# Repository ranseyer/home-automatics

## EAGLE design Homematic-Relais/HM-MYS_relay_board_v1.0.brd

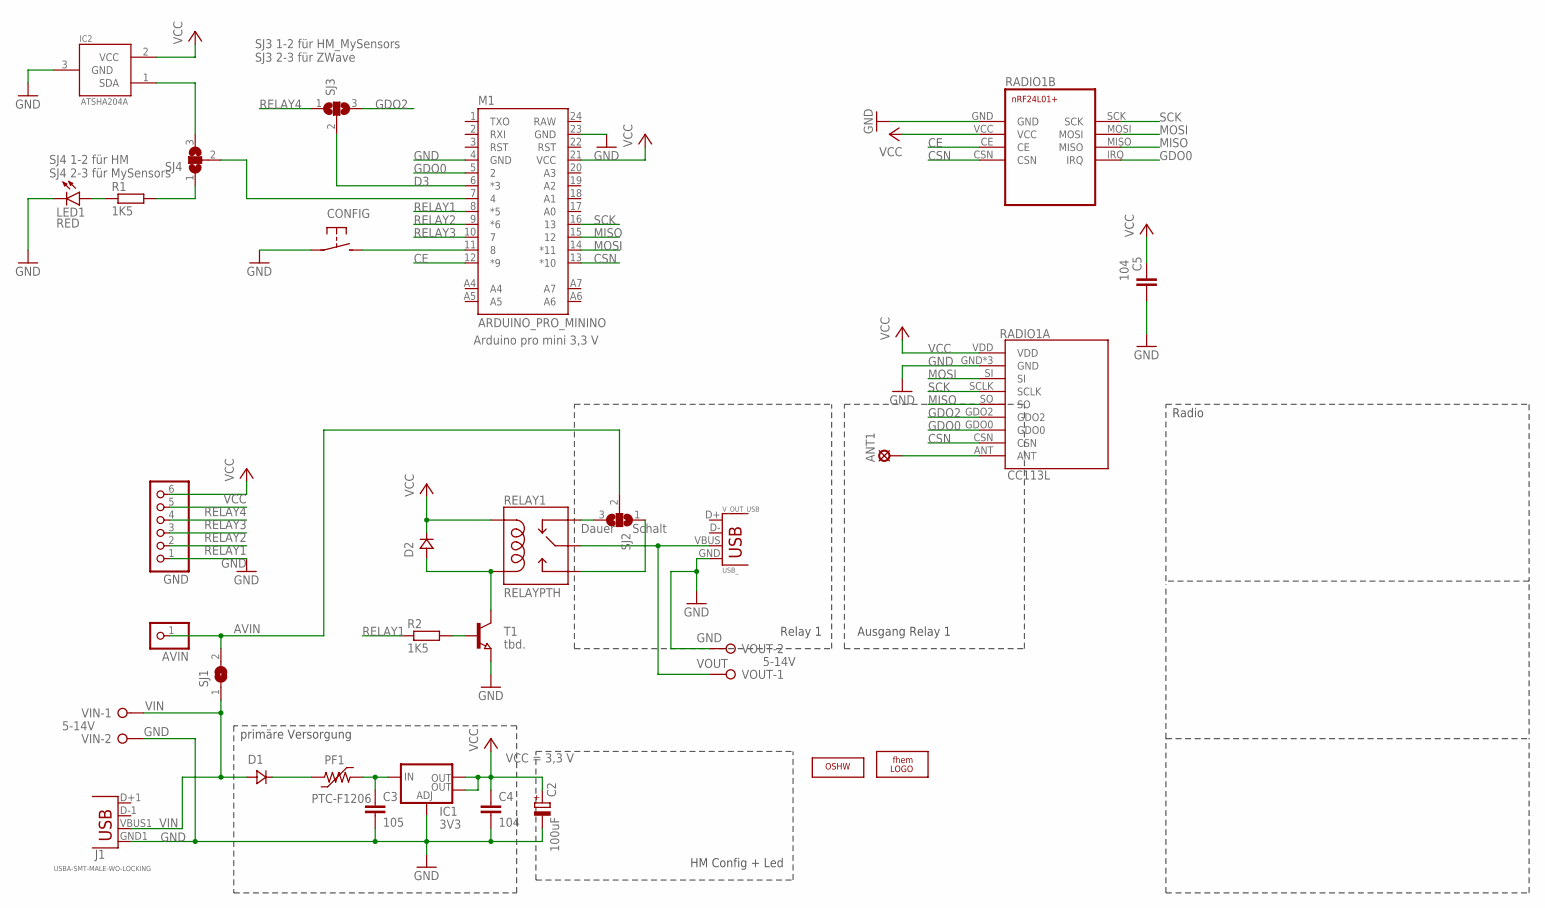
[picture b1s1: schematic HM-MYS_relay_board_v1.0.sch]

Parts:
ANT1: LSP10
AVIN: PINHD-1X1; 1X01
C2: 100uF; E2,5-6E
C3: 105; C0805
C4, C5: 104; C0805
CONFIG: TASTER-SMD
D1, D2: SS14; DO214
GND: PINHD-1X6_S; 1X06
IC1: 3V3; SOT223
IC2: ATSHA204A; SOT23-3
J1: USBA-SMT-MALE-WO-LOCKING; USB-A-SMT-MALE-NO_LOCKING
LED1: RED; LED-1206
LOGO2: LOGO_OSHWX0070; OSHW_6X70
M1: ARDUINO_PRO_MININO; ARDUINO_PRO_MINI_O
PF1: PTC-F1206; F1206
R1, R2: 1K5; R0805_SMALL_GAP
RADIO1A: CC113L
RADIO1B: NRF24L01+NRF24L01+MINI; NRF24L01+MINI
RELAY1: RELAYPTH; SRD-05VDC-SL-C
SJ1: SJ
SJ2, SJ3, SJ4: SJ2W; SJ_2
T1: tbd.; SOT89
U$2: LOGO_FHEMSTOP; LOGO_FHEM_3X3_STOP
VIN: W237-132
VOUT: W237-132
V_OUT_USB: USB_; USB-A-S-SILK-FEMALE

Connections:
ATSHA: IC2.1 (SDA), SJ4.3
AVIN: AVIN.1, SJ1.2, SJ2.2
CE: M1.12 (*9), RADIO1B.CE
CSN: M1.13 (*10), RADIO1A.CSN, RADIO1B.CSN
D3: M1.6 (*3), SJ3.2
D4: M1.7 (4), SJ4.2
DAUER: RELAY1.SWCLOSED (SWCLOSE), SJ2.3
GDO0: M1.5 (2), RADIO1A.GDO0, RADIO1B.IRQ
GDO2: RADIO1A.GDO2, SJ3.3
GND: C2.-, C3.2, C4.2, C5.2, CONFIG.1, GND.1, IC1.1 (ADJ), IC2.3 (GND), J1.GND1 (GND), LED1.C, M1.4 (GND), M1.23 (GND), RADIO1A.GND, RADIO1A.GND1 (GND), RADIO1A.GND2 (GND), RADIO1B.GND, T1.3 (E), VIN.2, VOUT.2, V_OUT_USB.GND
LED: R1.2, SJ4.1
MISO: M1.15 (12), RADIO1A.SO, RADIO1B.MISO
MOSI: M1.14 (*11), RADIO1A.SI, RADIO1B.MOSI
unnamed: CONFIG.2 (S), M1.11 (8)
unnamed: LED1.A, R1.1
unnamed: ANT1.1, RADIO1A.ANT
unnamed: D2.ANODE, RELAY1.COIL0, T1.2 (C)
unnamed: R2.2, T1.1 (B)
RELAY1: GND.2, M1.8 (*5), R2.1
RELAY2: GND.3, M1.9 (*6)
RELAY3: GND.4, M1.10 (7)
RELAY4: GND.5, SJ3.1
SCHALT: RELAY1.SWOPEN, SJ2.1
SCK: M1.16 (13), RADIO1A.SCLK, RADIO1B.SCK
VCC: C2.+, C4.1, C5.1, D2.CATHODE, GND.6, IC1.2 (OUT), IC1.4 (OUT), IC2.2 (VCC), M1.21 (VCC), RADIO1A.VDD, RADIO1B.VCC, RELAY1.COIL1
VIN: D1.ANODE, J1.VBUS1 (VBUS), SJ1.1, VIN.1
VOUT: RELAY1.SWCOMMON, VOUT.1, V_OUT_USB.VBUS
VREG_IN: C3.1, IC1.3 (IN), PF1.2
VUSB: D1.CATHODE, PF1.1

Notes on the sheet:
primäre Versorgung
5-14V
Radio
HM Config + Led
Relay 1
Ausgang Relay 1
Dauer
Schalt
SJ3 1-2 für HM_MySensors SJ3 2-3 für ZWave
Arduino pro mini 3,3 V
VCC = 3,3 V
SJ4 1-2 für HM SJ4 2-3 für MySensors

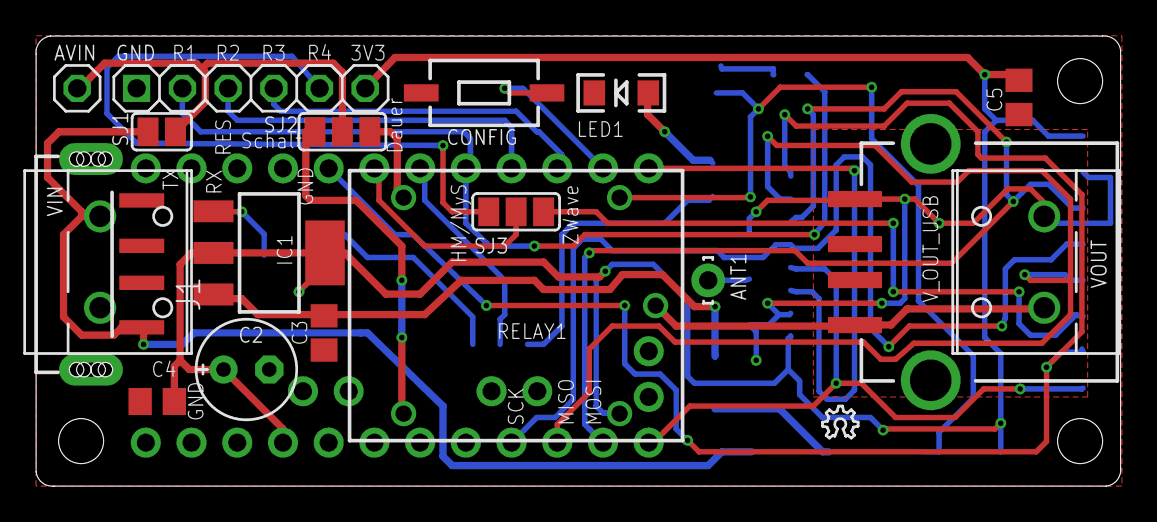
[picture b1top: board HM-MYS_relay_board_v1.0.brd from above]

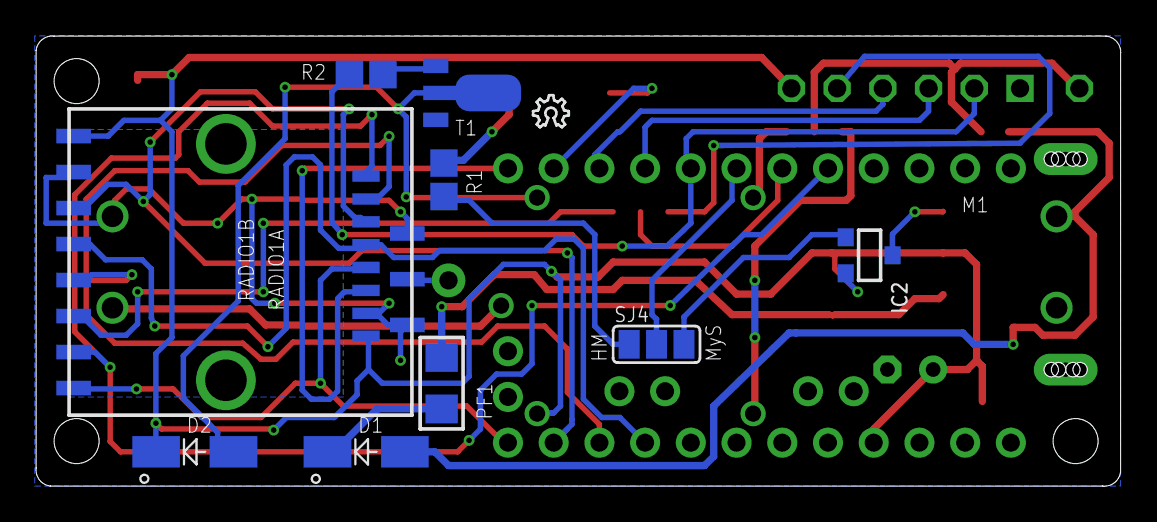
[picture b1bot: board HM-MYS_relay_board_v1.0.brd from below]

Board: 2 copper layers, 60.3 x 25.0 mm, 32 parts (12 on the bottom side), 29 nets.

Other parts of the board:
LOGO1: LOGO_OSHWX0070; OSHW_6X70

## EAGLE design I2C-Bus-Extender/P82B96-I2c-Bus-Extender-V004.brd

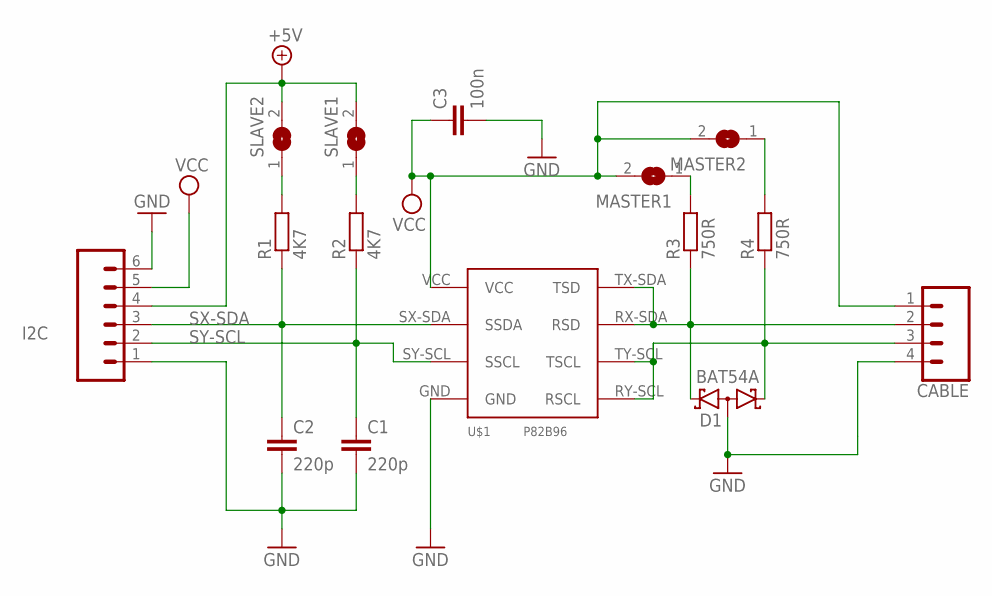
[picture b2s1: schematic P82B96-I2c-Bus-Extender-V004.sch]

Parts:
C1, C2: 220p; C0805K
C3: 100n; C0805K
CABLE: CONN_04LOCK_LONGPADS; 1X04_LOCK_LONGPADS
D1: BAT54A; SOT23
I2C: CONN_06LONGPADS; 1X06_LONGPADS
MASTER1, MASTER2: SJ
R1, R2: 4K7; R0805W
R3, R4: 750R; R0805W
SLAVE1, SLAVE2: SJ
U$1: P82B96-NEW; SOIC8

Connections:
+5V: I2C.4, SLAVE1.2, SLAVE2.2
GND: C1.2, C2.2, C3.2, CABLE.4, D1.3 (AA), I2C.1, I2C.6, U$1.GND
unnamed: R2.2, SLAVE1.1
unnamed: R1.2, SLAVE2.1
unnamed: MASTER2.1, R4.2
unnamed: MASTER1.1, R3.2
unnamed: CABLE.2, D1.2 (K2), R3.1, U$1.RX-SDA (RSD), U$1.TX-SDA (TSD)
unnamed: CABLE.3, D1.1 (K1), R4.1, U$1.RY-SCL (RSCL), U$1.TY-SCL (TSCL)
SX-SDA: C2.1, I2C.3, R1.1, U$1.SX-SDA (SSDA)
SY-SCL: C1.1, I2C.2, R2.1, U$1.SY-SCL (SSCL)
VCC: C3.1, CABLE.1, I2C.5, MASTER1.2, MASTER2.2, U$1.VCC

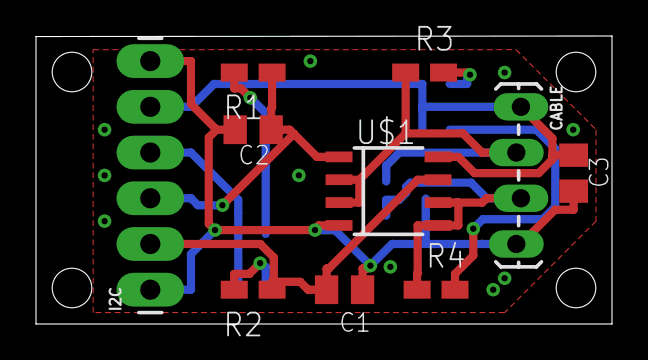
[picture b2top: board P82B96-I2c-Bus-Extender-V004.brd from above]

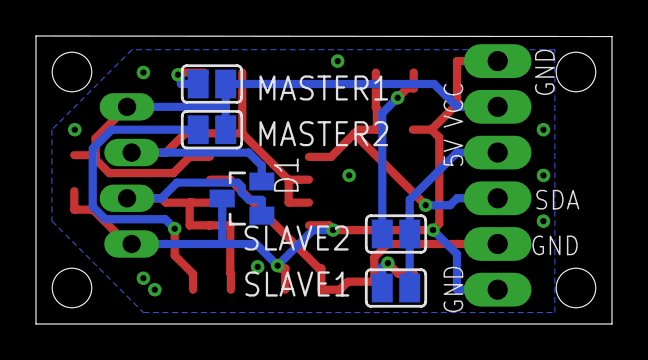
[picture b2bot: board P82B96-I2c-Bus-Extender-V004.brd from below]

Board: 2 copper layers, 32.0 x 16.0 mm, 15 parts (5 on the bottom side), 11 nets.

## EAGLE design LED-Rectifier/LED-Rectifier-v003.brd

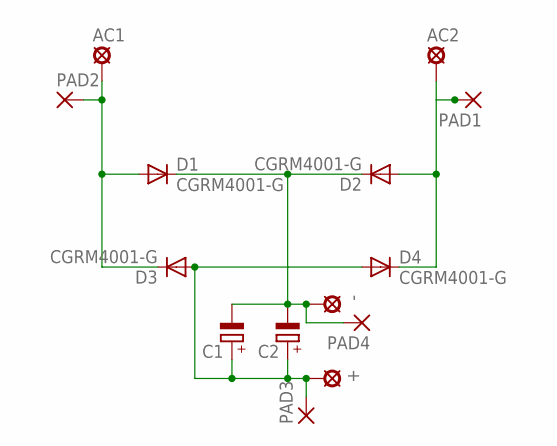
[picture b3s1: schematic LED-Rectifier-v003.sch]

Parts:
+: SE14
-: SE14
AC1, AC2: SE14
C1: CPOL-EU085CS-1AW; 085CS_1AW
C2: CPOL-EUE3.5-10; E3,5-10
D1, D2, D3, D4: CGRM4001-G; SOD-123_MINI-SMA
PAD1, PAD2, PAD3, PAD4: SMD5; SMD2,54-5,08

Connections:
+: +.MP, C1.+, C2.+, D3.A, D4.A, PAD3.1
-: -.MP, C1.-, C2.-, D1.C, D2.C, PAD4.1
AC1: AC1.MP, D1.A, D3.C, PAD2.1
AC2: AC2.MP, D2.A, D4.C, PAD1.1

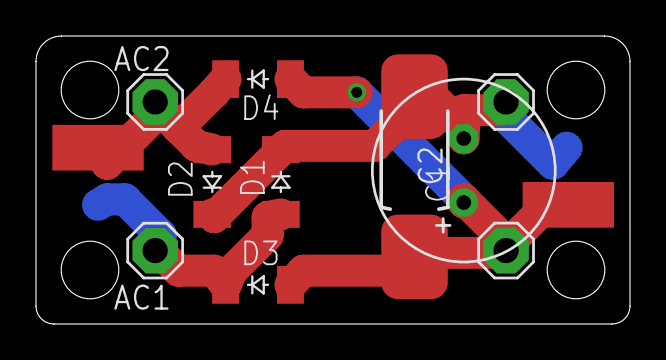
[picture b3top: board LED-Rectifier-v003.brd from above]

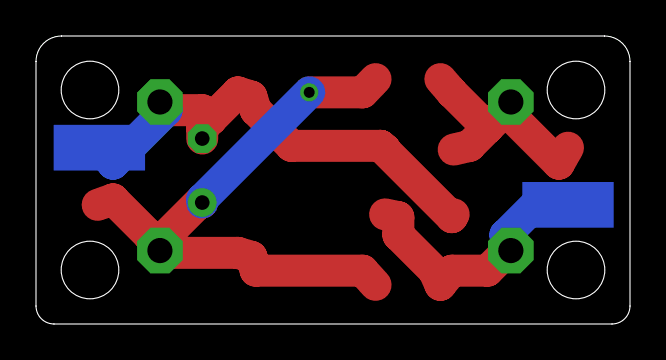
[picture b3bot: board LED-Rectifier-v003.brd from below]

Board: 2 copper layers, 33.0 x 16.0 mm, 14 parts (2 on the bottom side), 4 nets.

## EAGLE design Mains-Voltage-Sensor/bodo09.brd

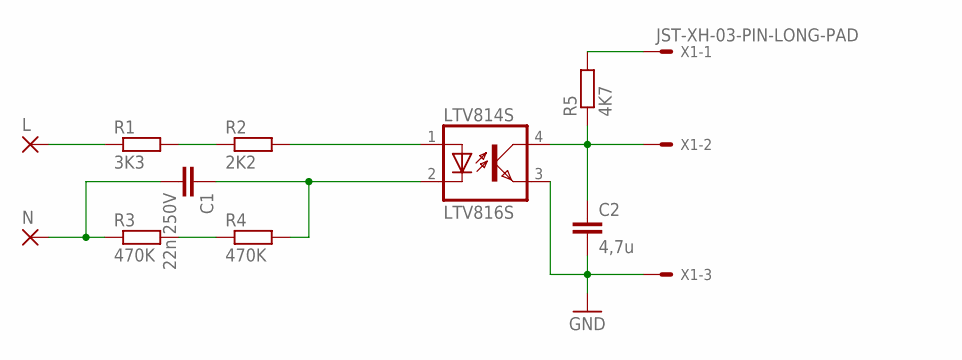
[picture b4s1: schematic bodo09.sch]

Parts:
C1: 22n 250V; C2220K
C2: 4,7u; C1206K
L: 3,81/1,4
LTV814S: LTV816S; SMD4
N: 3,81/1,4
R1: 3K3; R1206
R2: 2K2; R1206
R3, R4: 470K; R1206
R5: 4K7; R0805
X1: JST-XH-03-PIN-LONG-PAD; JST-XH-03-PACKAGE-LONG-PAD

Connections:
GND: C2.2, LTV814S.3 (EMIT), X1.3
unnamed: L.1, R1.1
unnamed: C1.2, N.1, R3.1
unnamed: R3.2, R4.1
unnamed: C1.1, LTV814S.2 (C), R4.2
unnamed: LTV814S.1 (A), R2.2
unnamed: R1.2, R2.1
unnamed: C2.1, LTV814S.4 (COL), R5.1, X1.2
unnamed: R5.2, X1.1

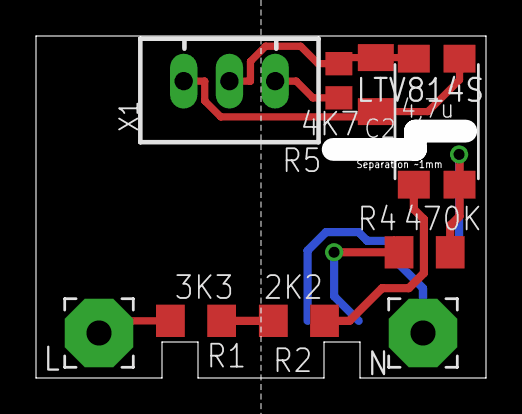
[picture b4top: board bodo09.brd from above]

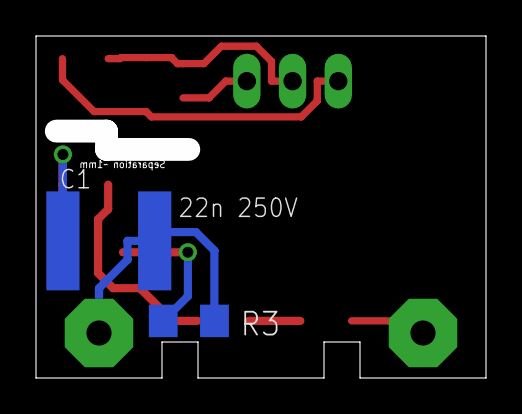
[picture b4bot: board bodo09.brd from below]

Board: 2 copper layers, 25.0 x 19.0 mm, 11 parts (2 on the bottom side), 9 nets.

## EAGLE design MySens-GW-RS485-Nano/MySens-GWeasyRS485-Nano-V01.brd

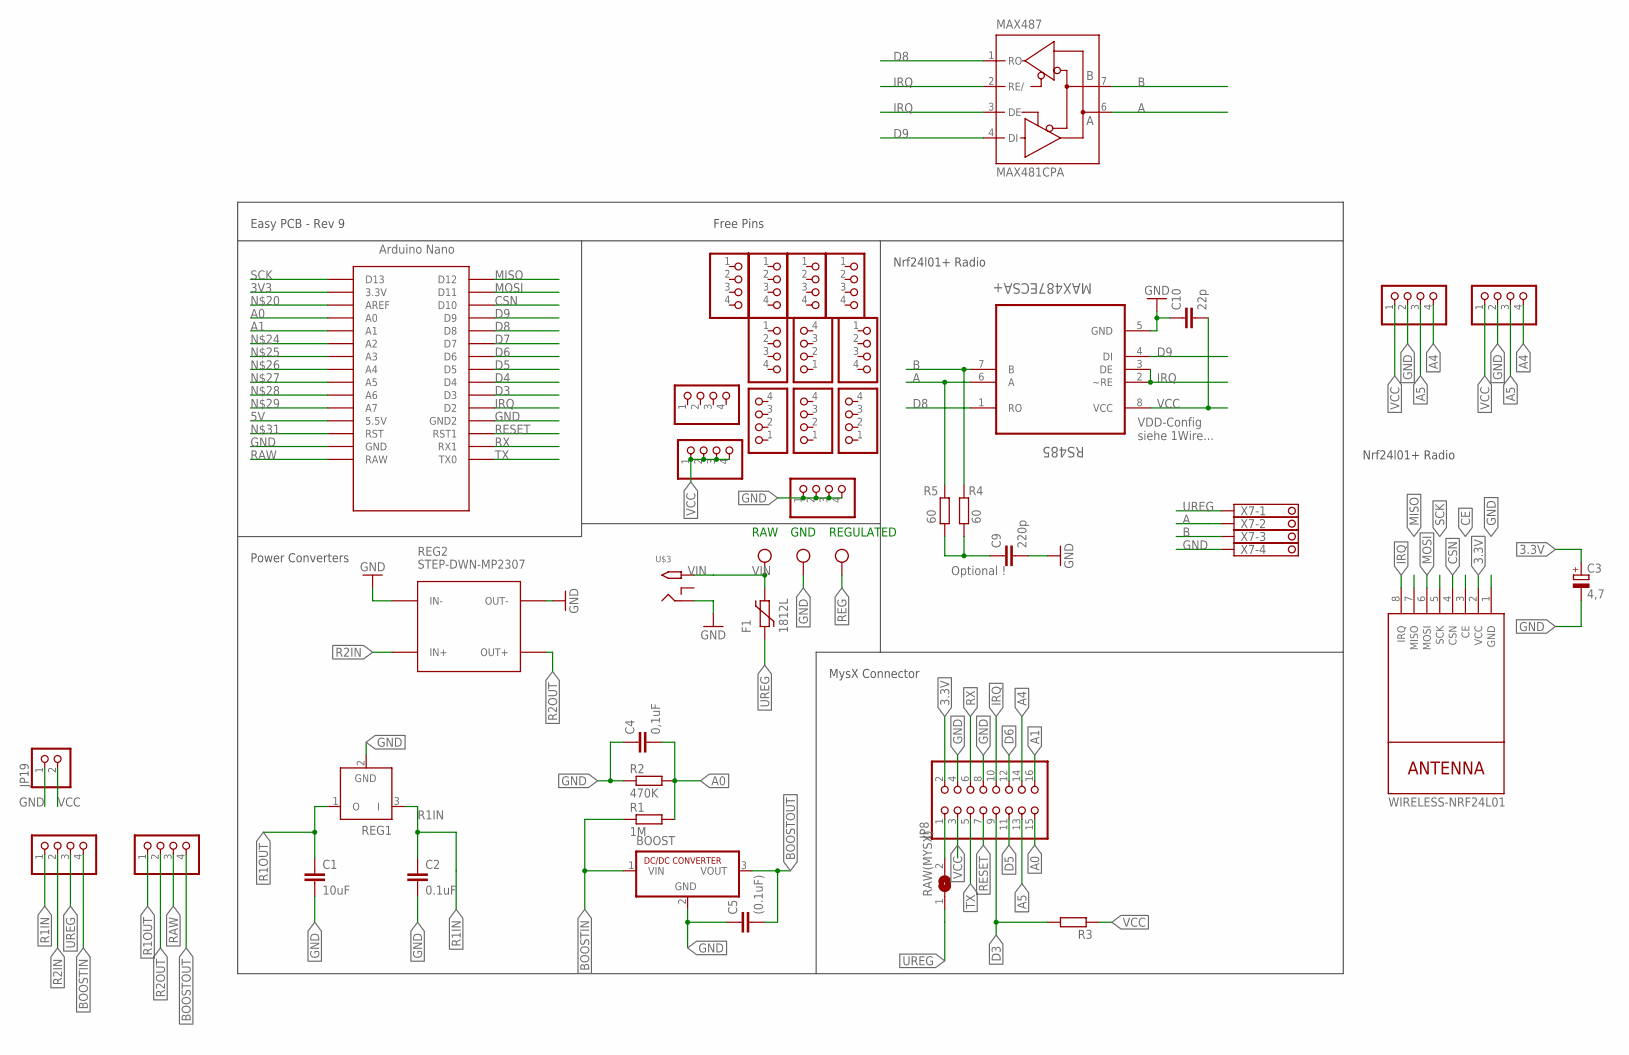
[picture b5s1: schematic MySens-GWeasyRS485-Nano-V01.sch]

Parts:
BOOST: R-78C1.8-1.0; SIP3
C1: 10uF; C1210
C2: 0.1uF; C1206
C3: 4,7; SMC_C
C4: 0,1uF; C1206
C5: (0.1uF); C1206
C9: 220p; C0805
C10: 22p; C0805
F1: 1812L
JP1, JP2, JP3, JP4, JP5, JP6, JP7, JP9, JP10, JP11, JP12, JP13, JP14, JP15, JP16, JP17, JP18: PINHD-1X04_2.54-S; 1X04-S
JP8: PINHD-2X08_2.54; 2X08
JP19: PINHD-1X2; 1X02
MAX487: MAX481CPA; DIL08
NRF24L01+: WIRELESS-NRF24L01
R1: 1M; R0805
R2: 470K; R0805
R3: R-EU_R0805; R0805
R4, R5: 60; R0805
RAW(MYSX): SJ
REG1: LP2950Z; TO92
REG2: STEP-DWN-MP2307; DC-DC-STEP-DOWN-MP2307
REGULATED: W237-103
RS485: MAX487ECSA+; SOIC127P600X175-8N
U$2: NANO
U$3: 2.1MMJACKTHM; PJ-102A
X7: 1751264

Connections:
3.3V: C3.+, JP8.2, NRF24L01+.2 (VCC)
3V3: U$2.3.3V
5V: U$2.5V (5.5V)
A: MAX487.6 (A), R5.2, RS485.6 (A), X7.2
A0: C4.2, JP8.15, R1.2, R2.2, U$2.A0
A1: JP8.16, U$2.A1
A4: JP6.4, JP8.14, JP10.4
A5: JP6.3, JP8.13, JP10.3
B: MAX487.7 (B), R4.2, RS485.7 (B), X7.3
BOOSTIN: BOOST.1 (VIN), JP2.4, R1.1
BOOSTOUT: BOOST.3 (VOUT), C5.2, JP4.4
CE: NRF24L01+.3 (CE)
CSN: NRF24L01+.4 (CSN), U$2.D10
D3: JP8.9, R3.2, U$2.D3
D4: U$2.D4
D5: JP8.11, U$2.D5
D6: JP8.12, U$2.D6
D7: U$2.D7
D8: MAX487.1 (RO), RS485.1 (RO), U$2.D8
D9: MAX487.4 (DI), RS485.4 (DI), U$2.D9
GND: BOOST.2 (GND), C1.2, C2.2, C3.-, C4.1, C5.1, C9.2, C10.1, JP1.1, JP1.2, JP1.3, JP1.4, JP6.2, JP8.4, JP8.8, JP10.2, JP19.1, MAX487.5 (GND), NRF24L01+.1 (GND), R2.1, REG1.2 (GND), REG2.IN-, REG2.OUT-, REGULATED.2, RS485.5 (GND), U$2.GND, U$2.GND1 (GND2), U$3.RING, X7.4
IRQ: JP8.10, MAX487.2 (RE/), MAX487.3 (DE), NRF24L01+.8 (IRQ), RS485.2 (~RE), RS485.3 (DE), U$2.D2
MISO: NRF24L01+.7 (MISO), U$2.D12
MOSI: NRF24L01+.6 (MOSI), U$2.D11
unnamed: JP8.1, RAW(MYSX).2
unnamed: C9.1, R4.1, R5.1
R1IN: C2.1, JP2.1, REG1.3 (I)
R1OUT: C1.1, JP4.1, REG1.1 (O)
R2IN: JP2.2, REG2.IN+
R2OUT: JP4.2, REG2.OUT+
RAW: JP4.3, U$2.RAW
REG: REGULATED.1
RESET: JP8.7, U$2.RST1
RX: JP8.6, U$2.RX1
SCK: NRF24L01+.5 (SCK), U$2.D13
TX: JP8.5, U$2.TX0
UREG: F1.P$1 (1), JP2.3, RAW(MYSX).1, X7.1
VCC: C10.2, JP3.1, JP3.2, JP3.3, JP3.4, JP6.1, JP8.3, JP10.1, JP19.2, MAX487.8 (VCC), R3.1, RS485.8 (VCC)
VIN: F1.P$2 (2), REGULATED.3, U$3.TIP

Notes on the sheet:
GND
RAW
REGULATED
Easy PCB - Rev 9
MysX Connector
Nrf24l01+ Radio
Power Converters
Free Pins
VDD-Config siehe 1Wire...
Optional !

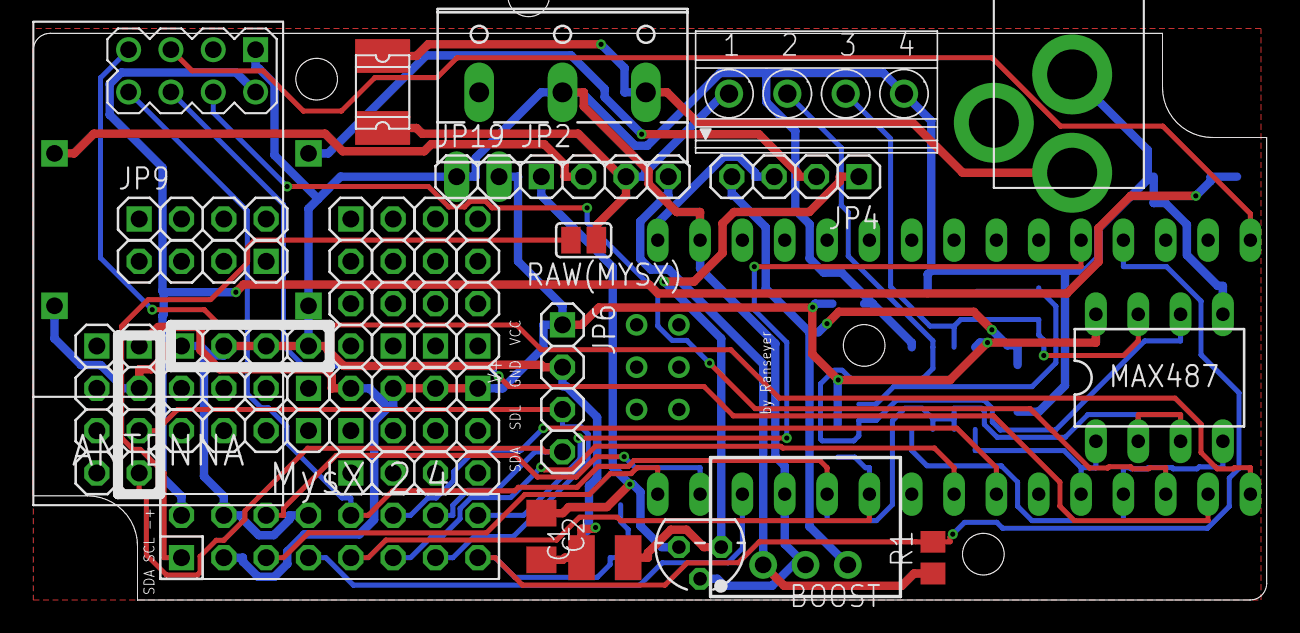
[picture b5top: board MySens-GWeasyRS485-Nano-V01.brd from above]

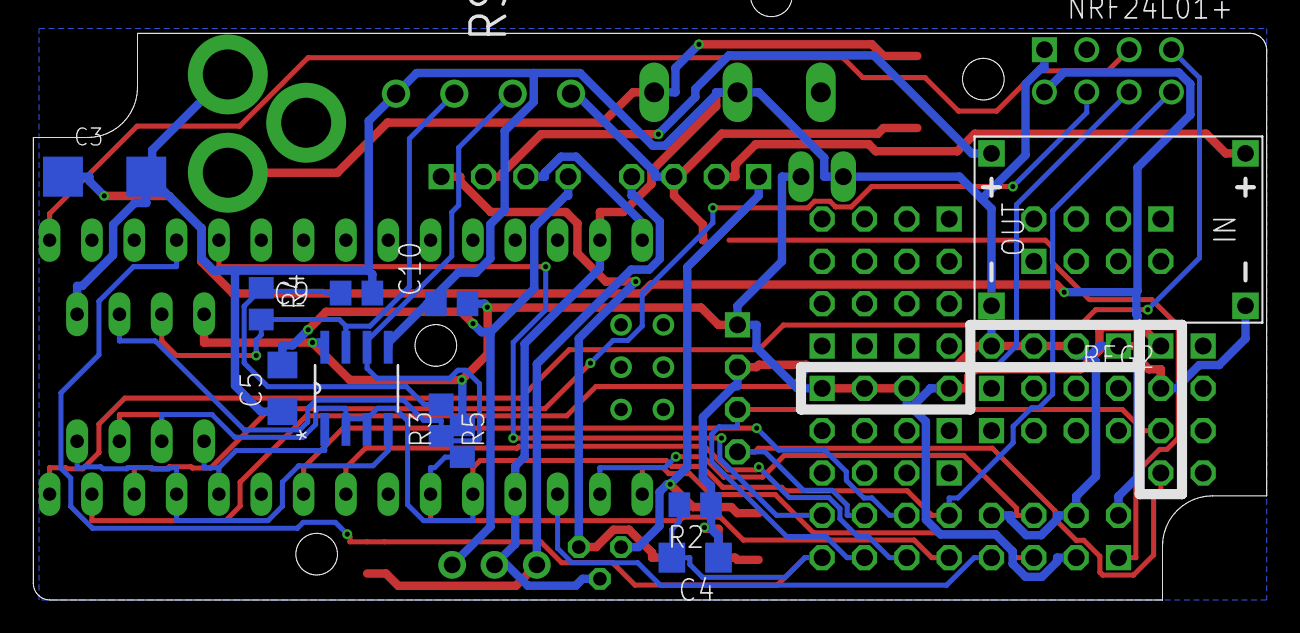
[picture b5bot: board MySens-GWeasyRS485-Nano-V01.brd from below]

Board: 2 copper layers, 74.0 x 34.0 mm, 43 parts (11 on the bottom side), 33 nets.

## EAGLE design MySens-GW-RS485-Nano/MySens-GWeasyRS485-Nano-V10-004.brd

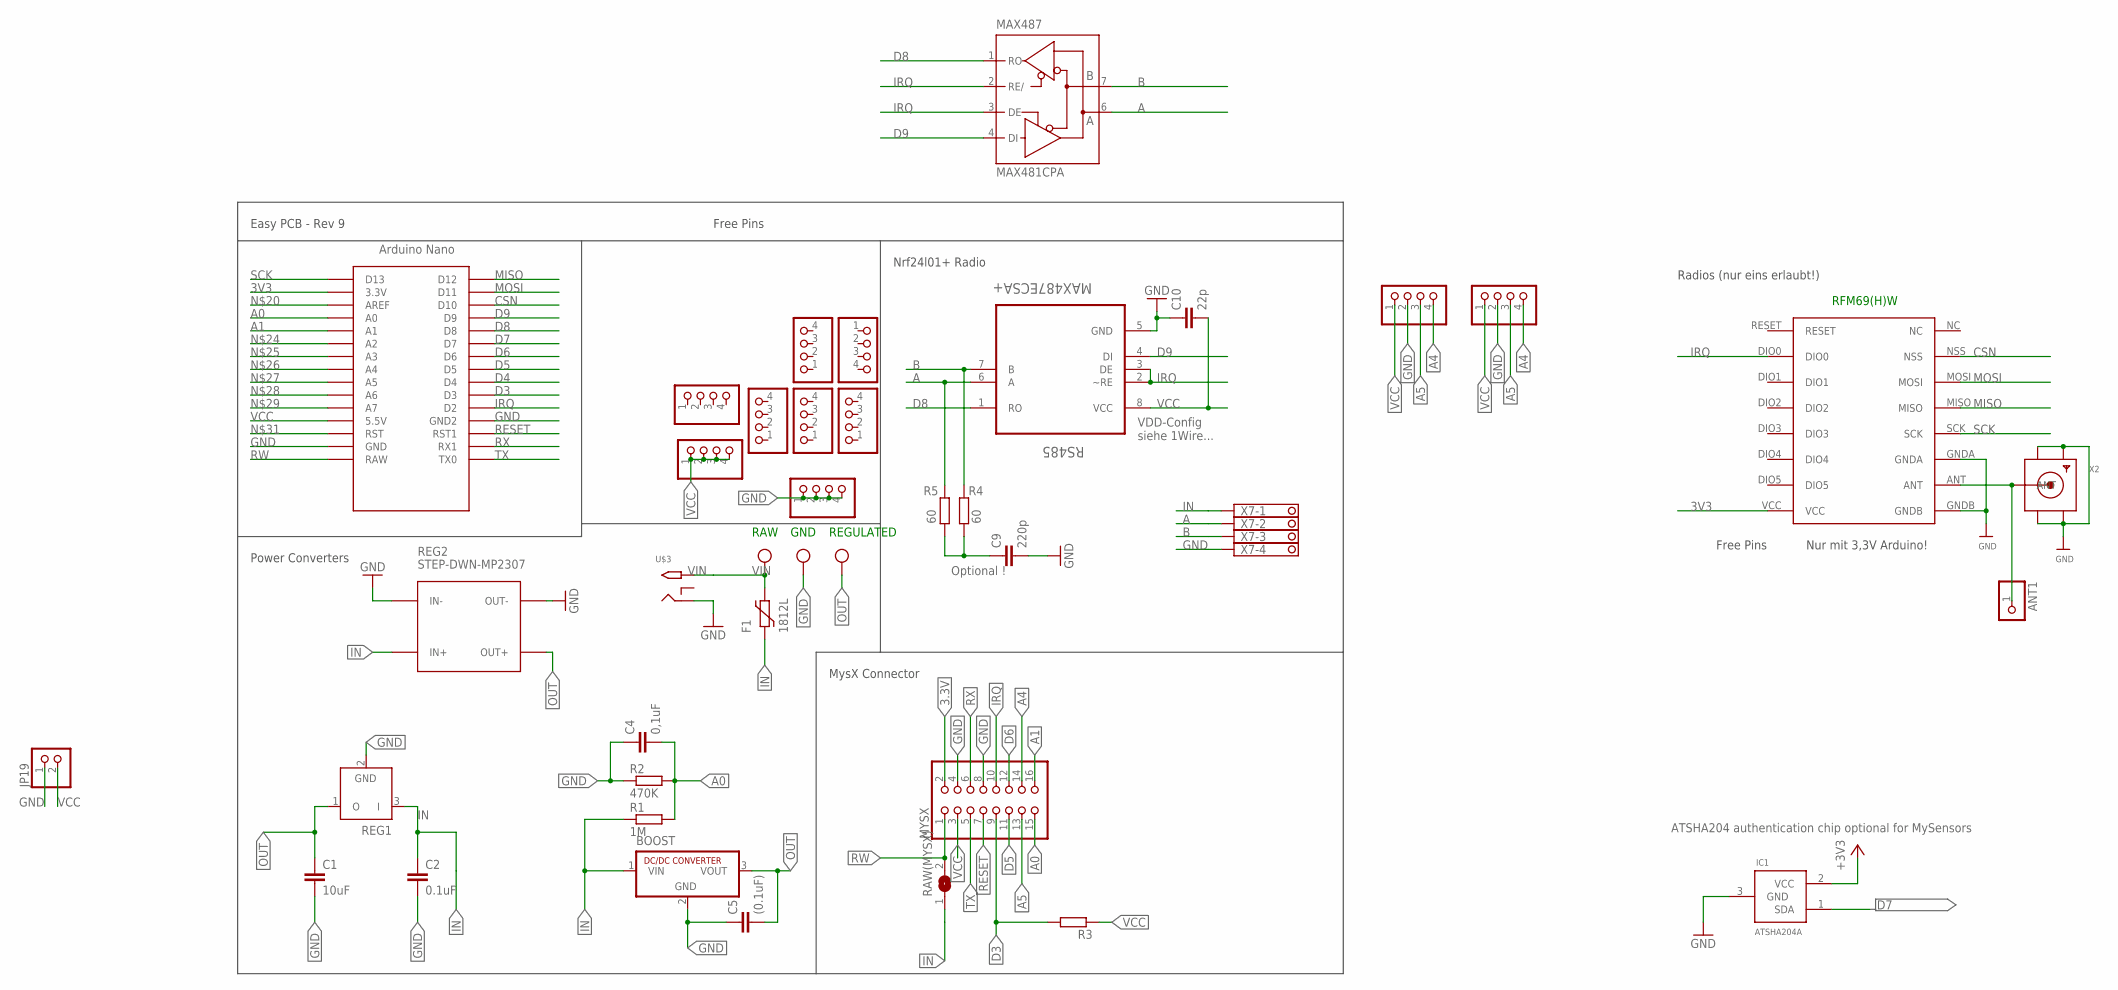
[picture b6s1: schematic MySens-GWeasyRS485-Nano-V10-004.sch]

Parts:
ANT1: PINHD-1X1; 1X01
BOOST: R-78C1.8-1.0; SIP3
C1: 10uF; C1210
C2: 0.1uF; C1206
C4: 0,1uF; C1206
C5: (0.1uF); C1206
C9: 220p; C0805
C10: 22p; C0805
F1: 1812L
IC1: ATSHA204A; SOT23
JP1, JP3, JP6, JP10, JP11, JP12, JP13, JP14, JP15, JP16: PINHD-1X04_2.54-S; 1X04-S
JP19: PINHD-1X2; 1X02
MAX487: MAX481CPA; DIL08
MYSX: PINHD-2X08_2.54; 2X08
R1: 1M; R0805
R2: 470K; R0805
R3: R-EU_R0805; R0805
R4, R5: 60; R0805
RAW(MYSX): SJ
REG1: LP2950Z; TO92
REG2: STEP-DWN-MP2307; DC-DC-STEP-DOWN-MP2307
REGULATED: W237-103
RFM69W: RFM69HW; RFM
RS485: MAX487ECSA+; SOIC127P600X175-8N
U$2: NANO
U$3: 2.1MMJACKTHM; PJ-102A
X2: SMACONNECTOR_EDGE; SMA_EDGELAUNCH
X7: 1751264

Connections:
3.3V: IC1.2 (VCC), MYSX.2
3V3: RFM69W.VCC, U$2.3.3V
A: MAX487.6 (A), R5.2, RS485.6 (A), X7.2
A0: C4.2, MYSX.15, R1.2, R2.2, U$2.A0
A1: MYSX.16, U$2.A1
A4: JP6.4, JP10.4, MYSX.14
A5: JP6.3, JP10.3, MYSX.13
B: MAX487.7 (B), R4.2, RS485.7 (B), X7.3
CSN: RFM69W.NSS, U$2.D10
D3: MYSX.9, R3.2, U$2.D3
D4: U$2.D4
D5: MYSX.11, U$2.D5
D6: MYSX.12, U$2.D6
D7: IC1.1 (SDA), U$2.D7
D8: MAX487.1 (RO), RS485.1 (RO), U$2.D8
D9: MAX487.4 (DI), RS485.4 (DI), U$2.D9
GND: BOOST.2 (GND), C1.2, C2.2, C4.1, C5.1, C9.2, C10.1, IC1.3 (GND), JP1.1, JP1.2, JP1.3, JP1.4, JP6.2, JP10.2, JP19.1, MAX487.5 (GND), MYSX.4, MYSX.8, R2.1, REG1.2 (GND), REG2.IN-, REG2.OUT-, REGULATED.2, RFM69W.GNDA, RFM69W.GNDB, RS485.5 (GND), U$2.GND, U$2.GND1 (GND2), U$3.RING, X2.GND@1 (GND4), X2.GND@2 (GND3), X2.GND@3 (GND2), X2.GND@4 (GND1), X7.4
IN: BOOST.1 (VIN), C2.1, F1.P$1 (1), R1.1, RAW(MYSX).1, REG1.3 (I), REG2.IN+, X7.1
IRQ: MAX487.2 (RE/), MAX487.3 (DE), MYSX.10, RFM69W.DIO0, RS485.2 (~RE), RS485.3 (DE), U$2.D2
MISO: RFM69W.MISO, U$2.D12
MOSI: RFM69W.MOSI, U$2.D11
unnamed: ANT1.1, RFM69W.ANT, X2.P (ANT)
unnamed: C9.1, R4.1, R5.1
OUT: BOOST.3 (VOUT), C1.1, C5.2, REG1.1 (O), REG2.OUT+, REGULATED.1
RESET: MYSX.7, U$2.RST1
RW: MYSX.1, RAW(MYSX).2, U$2.RAW
RX: MYSX.6, U$2.RX1
SCK: RFM69W.SCK, U$2.D13
TX: MYSX.5, U$2.TX0
VCC: C10.2, JP3.1, JP3.2, JP3.3, JP3.4, JP6.1, JP10.1, JP19.2, MAX487.8 (VCC), MYSX.3, R3.1, RS485.8 (VCC), U$2.5V (5.5V)
VIN: F1.P$2 (2), REGULATED.3, U$3.TIP

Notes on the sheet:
GND
RAW
REGULATED
Easy PCB - Rev 9
MysX Connector
Nrf24l01+ Radio
Power Converters
Free Pins
VDD-Config siehe 1Wire...
Optional !
ATSHA204 authentication chip optional for MySensors
RFM69(H)W
Nur mit 3,3V Arduino!
Radios (nur eins erlaubt!)

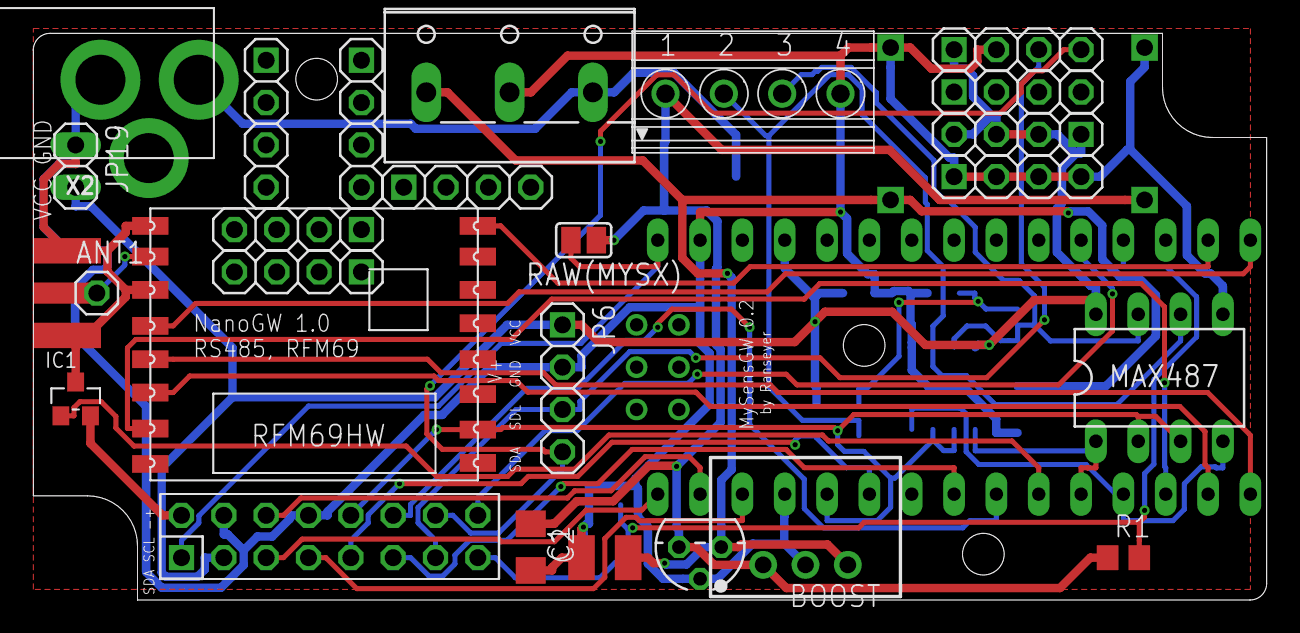
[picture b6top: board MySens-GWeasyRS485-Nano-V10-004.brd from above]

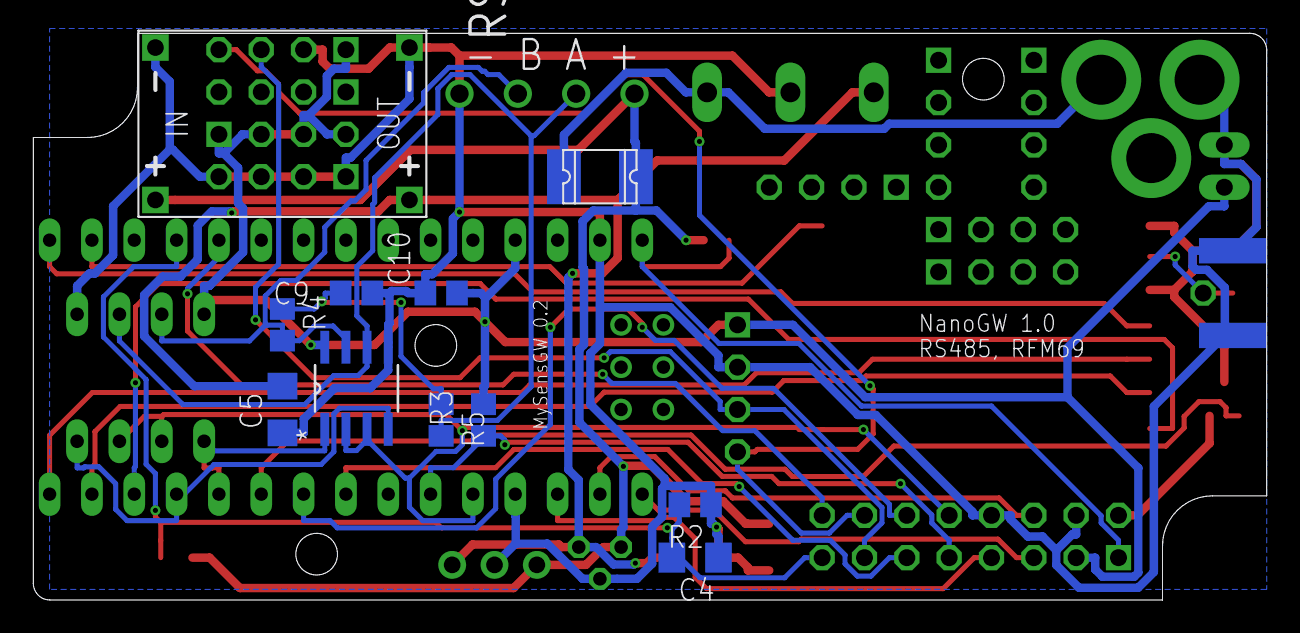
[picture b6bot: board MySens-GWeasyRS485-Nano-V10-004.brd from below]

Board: 2 copper layers, 74.0 x 34.0 mm, 38 parts (11 on the bottom side), 30 nets.

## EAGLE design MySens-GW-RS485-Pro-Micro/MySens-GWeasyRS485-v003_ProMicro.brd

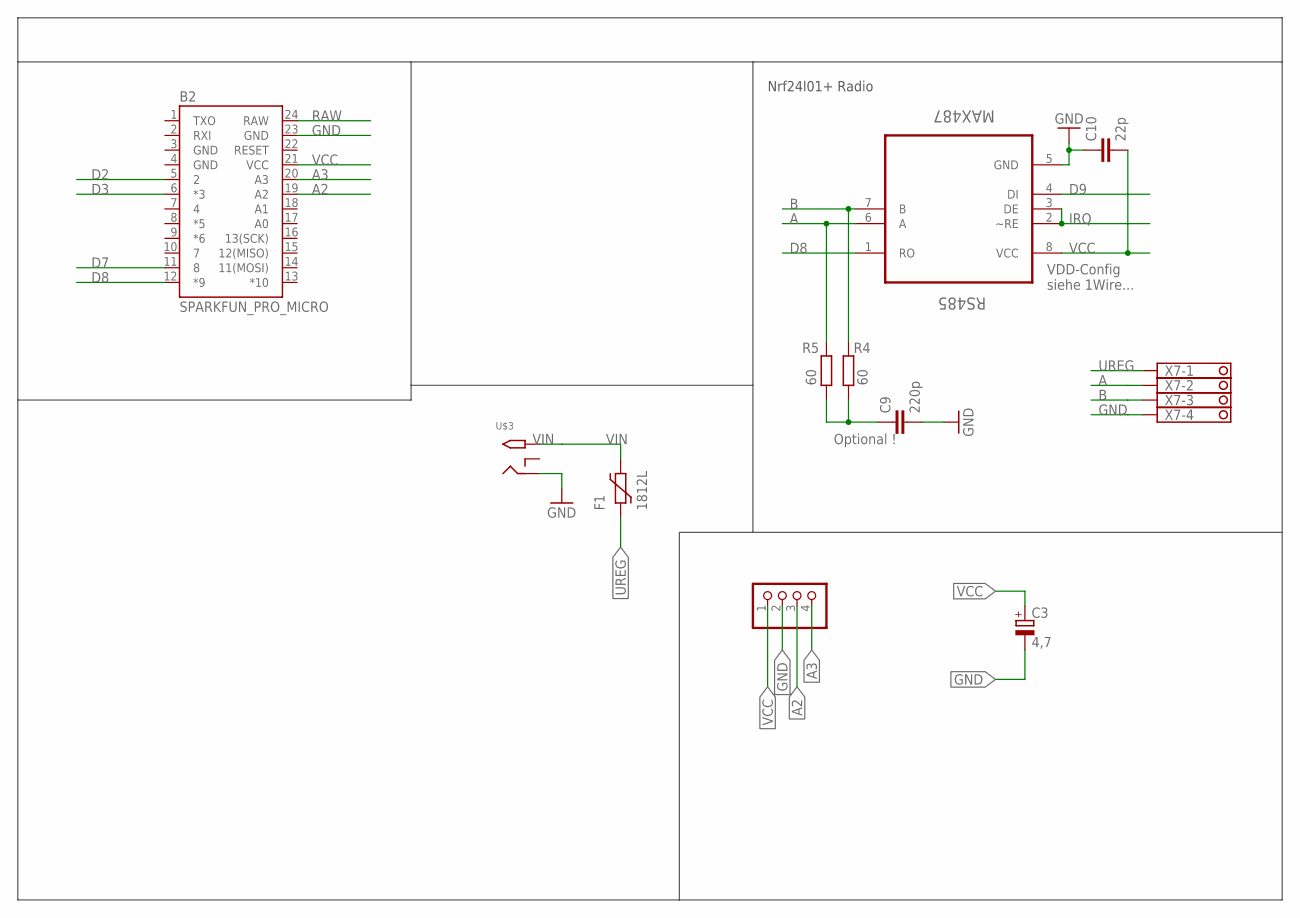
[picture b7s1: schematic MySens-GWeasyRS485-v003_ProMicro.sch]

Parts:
B2: SPARKFUN_PRO_MICRO
C3: 4,7; SMC_C
C9: 220p; C0805
C10: 22p; C0805
F1: 1812L
JP10: PINHD-1X04_2.54-S; 1X04-S
R4, R5: 60; R0805
RS485: MAX487; SOIC127P600X175-8N
U$3: 2.1MMJACKTHM; PJ-102A
X7: 1751264

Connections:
A: R5.2, RS485.6 (A), X7.2
A2: B2.19 (A2), JP10.3
A3: B2.20 (A3), JP10.4
B: R4.2, RS485.7 (B), X7.3
D2: B2.5 (2)
D3: B2.6 (*3)
D7: B2.11 (8)
D8: B2.12 (*9), RS485.1 (RO)
D9: RS485.4 (DI)
GND: B2.3 (GND), B2.4 (GND), B2.23 (GND), C3.-, C9.2, C10.1, JP10.2, RS485.5 (GND), U$3.RING, X7.4
IRQ: RS485.2 (~RE), RS485.3 (DE)
unnamed: C9.1, R4.1, R5.1
RAW: B2.24 (RAW)
UREG: F1.P$1 (1), X7.1
VCC: B2.21 (VCC), C3.+, C10.2, JP10.1, RS485.8 (VCC)
VIN: F1.P$2 (2), U$3.TIP

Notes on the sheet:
Nrf24l01+ Radio
VDD-Config siehe 1Wire...
Optional !

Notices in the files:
parts and their libraries:
SparkFun-PowerIC: Licensing: Creative Commons ShareAlike 4.0 International - https://creativecommons.org/licenses/by-sa/4.0
polyswitch: Copyright (C) 2008, Bob Starr
diy-modules: Released under the Creative Commons Attribution 4.0 International License: http://creativecommons.org/licenses/by/4.0
